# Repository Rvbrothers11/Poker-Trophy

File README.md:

# Poker-Trophy
A 3D printed small Poker Trophy

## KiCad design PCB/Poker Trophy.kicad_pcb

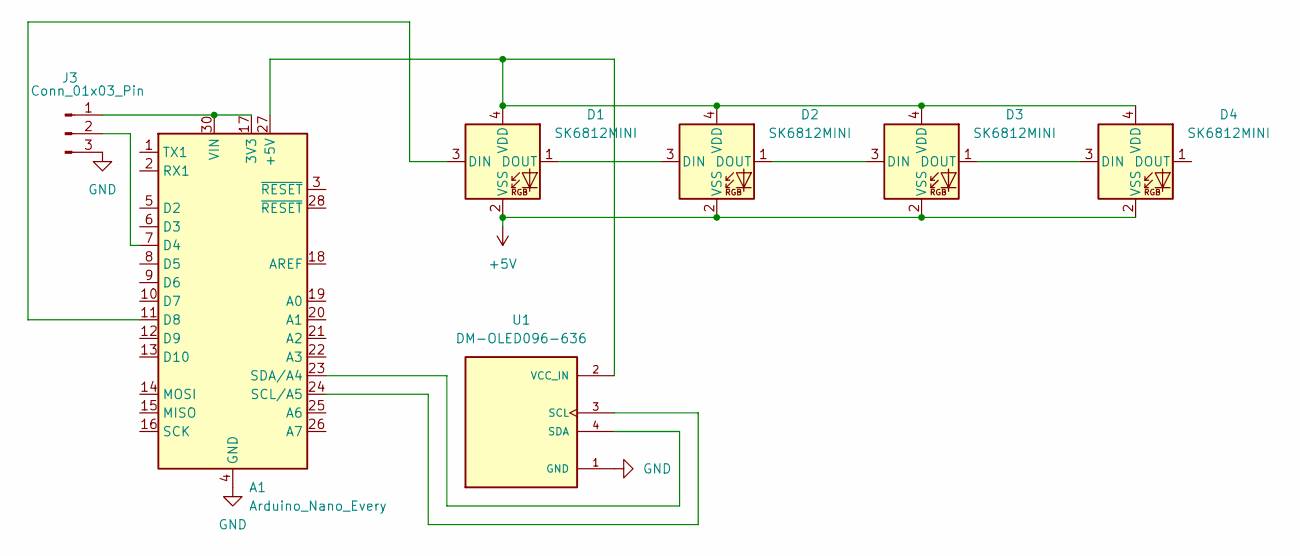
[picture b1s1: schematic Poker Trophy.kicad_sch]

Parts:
A1: Arduino_Nano_Every; Arduino_Nano
D1, D2, D3, D4: SK6812MINI; LED_SK6812MINI_PLCC4_3.5x3.5mm_P1.75mm
J3: Conn_01x03_Pin; FanPinHeader_1x03_P2.54mm_Vertical
U1: DM-OLED096-636; MODULE_DM-OLED096-636; PARTREV 2018-09-10

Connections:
+5V: D1.2 (VSS), D2.2 (VSS), D3.2 (VSS), D4.2 (VSS)
GND: A1.4 (GND), A1.29 (GND), J3.3, U1.1 (GND)
unnamed: A1.17 (3V3), A1.30 (VIN), J3.1
unnamed: A1.27 (+5V), D1.4 (VDD), D2.4 (VDD), D3.4 (VDD), D4.4 (VDD), U1.2 (VCC_IN)
unnamed: A1.7 (D4), J3.2
unnamed: A1.11 (D8), D1.3 (DIN)
unnamed: A1.24 (SCL/A5), U1.3 (SCL)
unnamed: A1.23 (SDA/A4), U1.4 (SDA)
unnamed: D1.1 (DOUT), D2.3 (DIN)
unnamed: D2.1 (DOUT), D3.3 (DIN)
unnamed: D3.1 (DOUT), D4.3 (DIN)

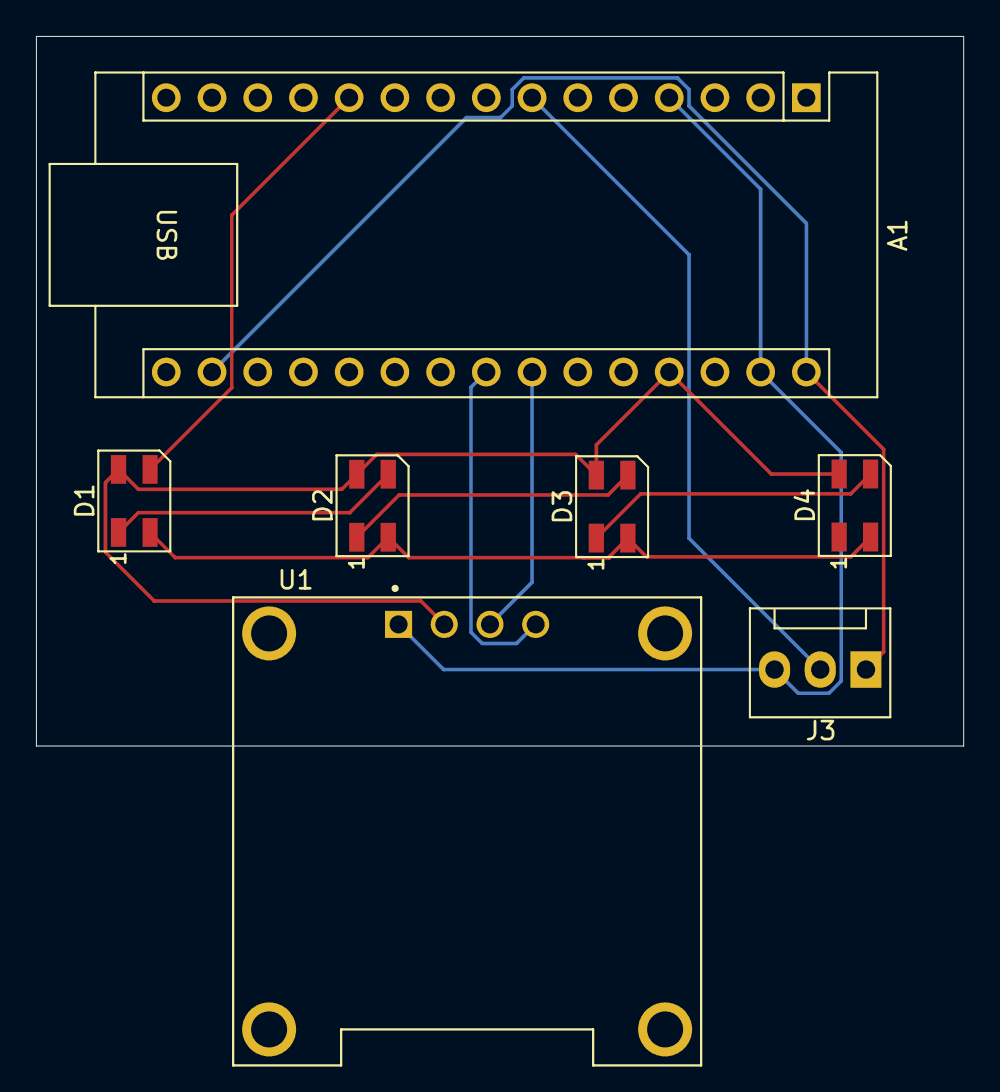
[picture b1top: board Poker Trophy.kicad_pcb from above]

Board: 2 copper layers, 51.5 x 39.4 mm, 7 parts (0 on the bottom side), 11 nets.

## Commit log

2026-05-22 Create a
2026-05-22 Enhance README with project details and BOM
    Added detailed project description, usage instructions, and Bill of Materials (BOM) table with cost information.
2026-06-05 Enhance README with assembly steps and BOM
    Updated README.md to include detailed assembly instructions, images, and a Bill of Materials (BOM) table.
